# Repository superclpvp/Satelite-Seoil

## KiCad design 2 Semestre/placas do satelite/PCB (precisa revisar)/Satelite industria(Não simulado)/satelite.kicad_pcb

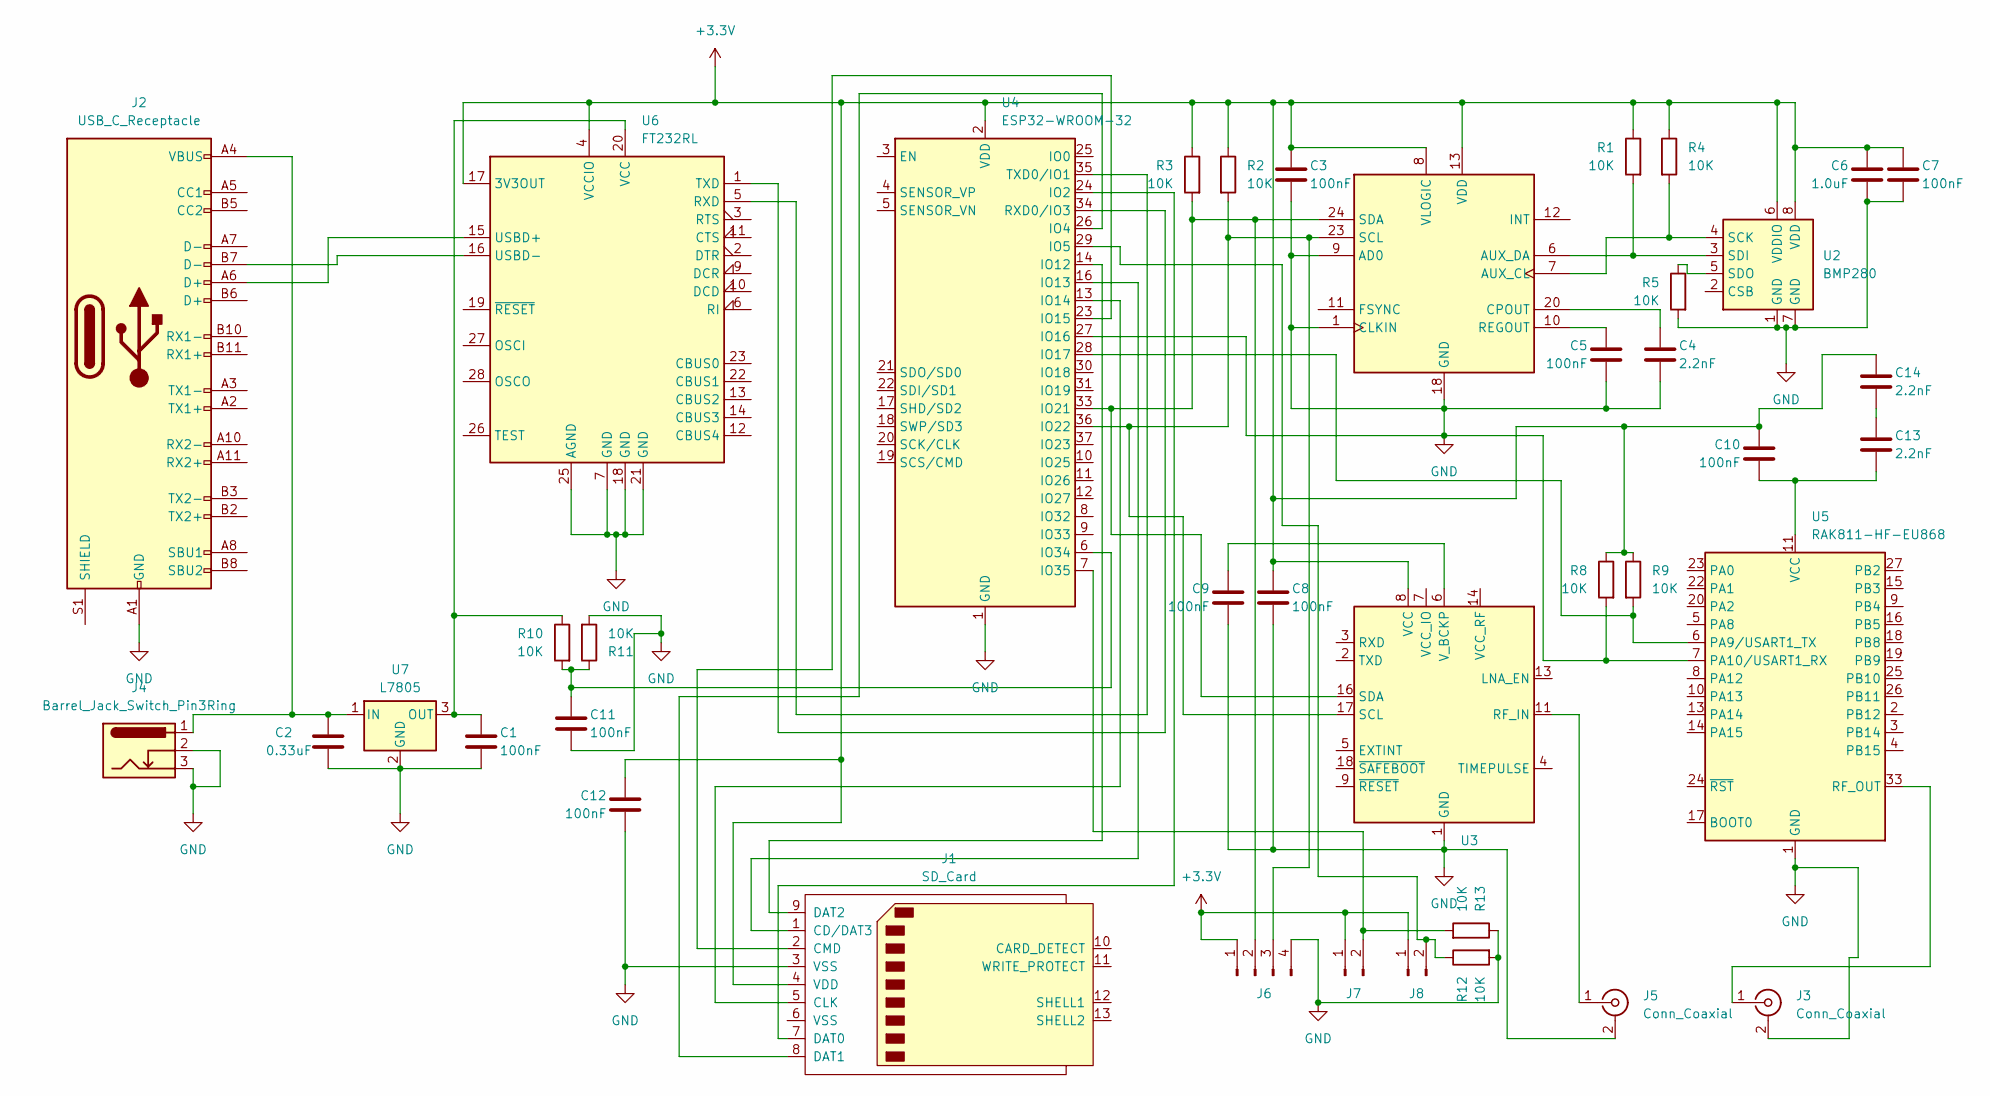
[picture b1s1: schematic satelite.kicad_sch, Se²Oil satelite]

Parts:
C1, C3, C5, C7, C8, C9, C10, C11, C12: 100nF; C_0805_2012Metric
C2: 0.33uF; C_0201_0603Metric
C4, C13, C14: 2.2nF; C_0201_0603Metric
C6: 1.0uF; C_0201_0603Metric
J1: SD_Card; microSD_HC_Hirose_DM3D-SF
J2: USB_C_Receptacle; USB_C_Receptacle_GCT_USB4085
J3, J5: Conn_Coaxial; U.FL_Hirose_U.FL-R-SMT-1_Vertical
J4: Barrel_Jack_Switch_Pin3Ring; BarrelJack_Horizontal
J6: Conn_01x04_Pin; PinHeader_1x04_P1.00mm_Vertical
J7, J8: Conn_01x02_Pin; PinHeader_1x02_P1.00mm_Vertical
R1, R2, R3, R4, R5, R8, R9, R10, R11, R12, R13: 10K; R_0805_2012Metric
U1: MPU-6050; InvenSense_QFN-24_4x4mm_P0.5mm
U2: BMP280; Bosch_LGA-8_2x2.5mm_P0.65mm_ClockwisePinNumbering
U3: MAX-M8Q; ublox_MAX
U4: ESP32-WROOM-32
U5: RAK811-HF-EU868; RAK811
U6: FT232RL; SSOP-28_5.3x10.2mm_P0.65mm
U7: L7805; TO-263-2

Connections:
+3.3V: C3.1, C6.1, C7.1, C8.1, C10.1, C12.1, C14.1, J1.4 (VDD), J6.1, J7.1, J8.1, R1.1, R2.1, R3.1, R4.1, R8.1, R9.1, U1.8 (VLOGIC), U1.13 (VDD), U2.6 (VDDIO), U2.8 (VDD), U3.8 (VCC), U4.2 (VDD), U6.4 (VCCIO), U6.17 (3V3OUT)
GND: C1.2, C2.2, C3.2, C4.2, C5.2, C6.2, C7.2, C8.2, C9.2, C11.2, C12.2, J1.3 (VSS), J2.A1 (GND), J2.A12 (GND), J2.B1 (GND), J2.B12 (GND), J3.2 (Ext), J4.2, J4.3, J5.2 (Ext), J6.4, R5.2, R8.2, R11.2, R12.2, R13.1, U1.1 (CLKIN), U1.9 (AD0), U1.18 (GND), U2.1 (GND), U2.7 (GND), U3.1 (GND), U3.10 (GND), U3.12 (GND), U4.1 (GND), U4.15 (GND), U4.27 (IO16), U4.38 (GND), U4.39 (GND), U5.1 (GND), U5.7 (PA10/USART1_RX), U5.12 (GND), U5.21 (GND), U5.28 (GND), U5.29 (GND), U5.30 (GND), U5.31 (GND), U5.32 (GND), U5.34 (GND), U6.7 (GND), U6.18 (GND), U6.21 (GND), U6.25 (AGND), U7.2 (GND)
unnamed: C13.1, C14.2
unnamed: J1.1 (CD/DAT3), U4.16 (IO13)
unnamed: J1.5 (CLK), U4.13 (IO14)
unnamed: J1.2 (CMD), U4.23 (IO15)
unnamed: J1.7 (DAT0), U4.24 (IO2)
unnamed: J1.8 (DAT1), U4.26 (IO4)
unnamed: J1.9 (DAT2), U4.14 (IO12)
unnamed: J3.1 (In), U5.33 (RF_OUT)
unnamed: J5.1 (In), U3.11 (RF_IN)
unnamed: J6.2, R3.2, U1.24 (SDA), U3.16 (SDA), U4.33 (IO21)
unnamed: J6.3, R2.2, U1.23 (SCL), U3.17 (SCL), U4.36 (IO22)
unnamed: J7.2, R13.2, U4.7 (IO35)
unnamed: J8.2, R12.1, U4.29 (IO5)
unnamed: R4.2, U1.7 (AUX_CL), U2.4 (SCK)
unnamed: R1.2, U1.6 (AUX_DA), U2.3 (SDI)
unnamed: C4.1, U1.20 (CPOUT)
unnamed: C5.1, U1.10 (REGOUT)
unnamed: R5.1, U2.5 (SDO)
unnamed: C9.1, U3.6 (V_BCKP)
unnamed: R9.2, U4.28 (IO17), U5.6 (PA9/USART1_TX)
unnamed: C11.1, R10.2, R11.1, U4.6 (IO34)
unnamed: U4.34 (RXD0/IO3), U6.1 (TXD)
unnamed: U4.35 (TXD0/IO1), U6.5 (RXD)
unnamed: C10.2, C13.2, U5.11 (VCC)
unnamed: J2.A6 (D+), U6.15 (USBD+)
unnamed: J2.B7 (D-), U6.16 (USBD-)
unnamed: C1.1, R10.1, U6.20 (VCC), U7.3 (OUT)
unnamed: C2.1, J2.A4 (VBUS), J2.A9 (VBUS), J2.B4 (VBUS), J2.B9 (VBUS), J4.1, U7.1 (IN)

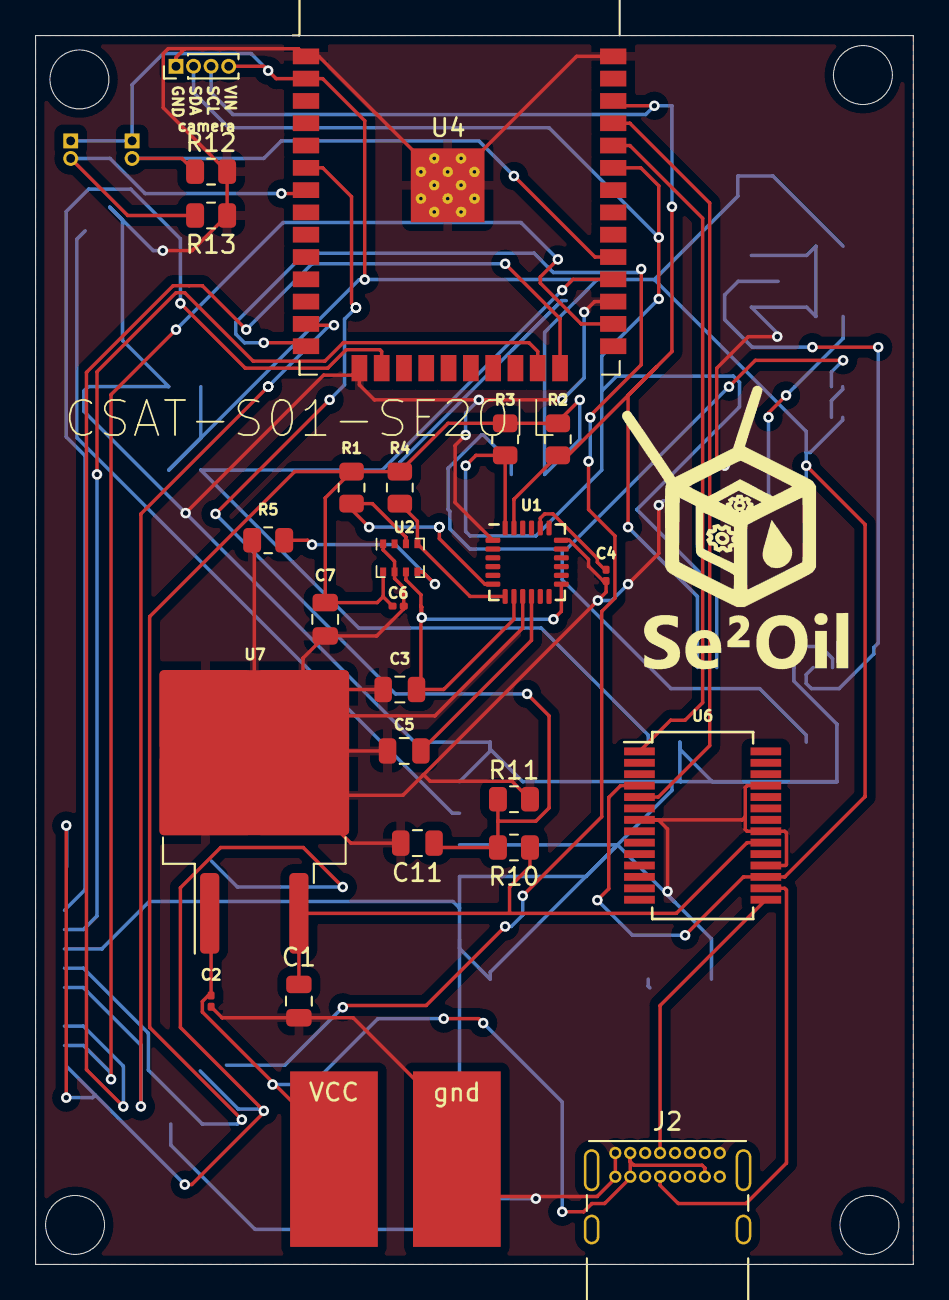
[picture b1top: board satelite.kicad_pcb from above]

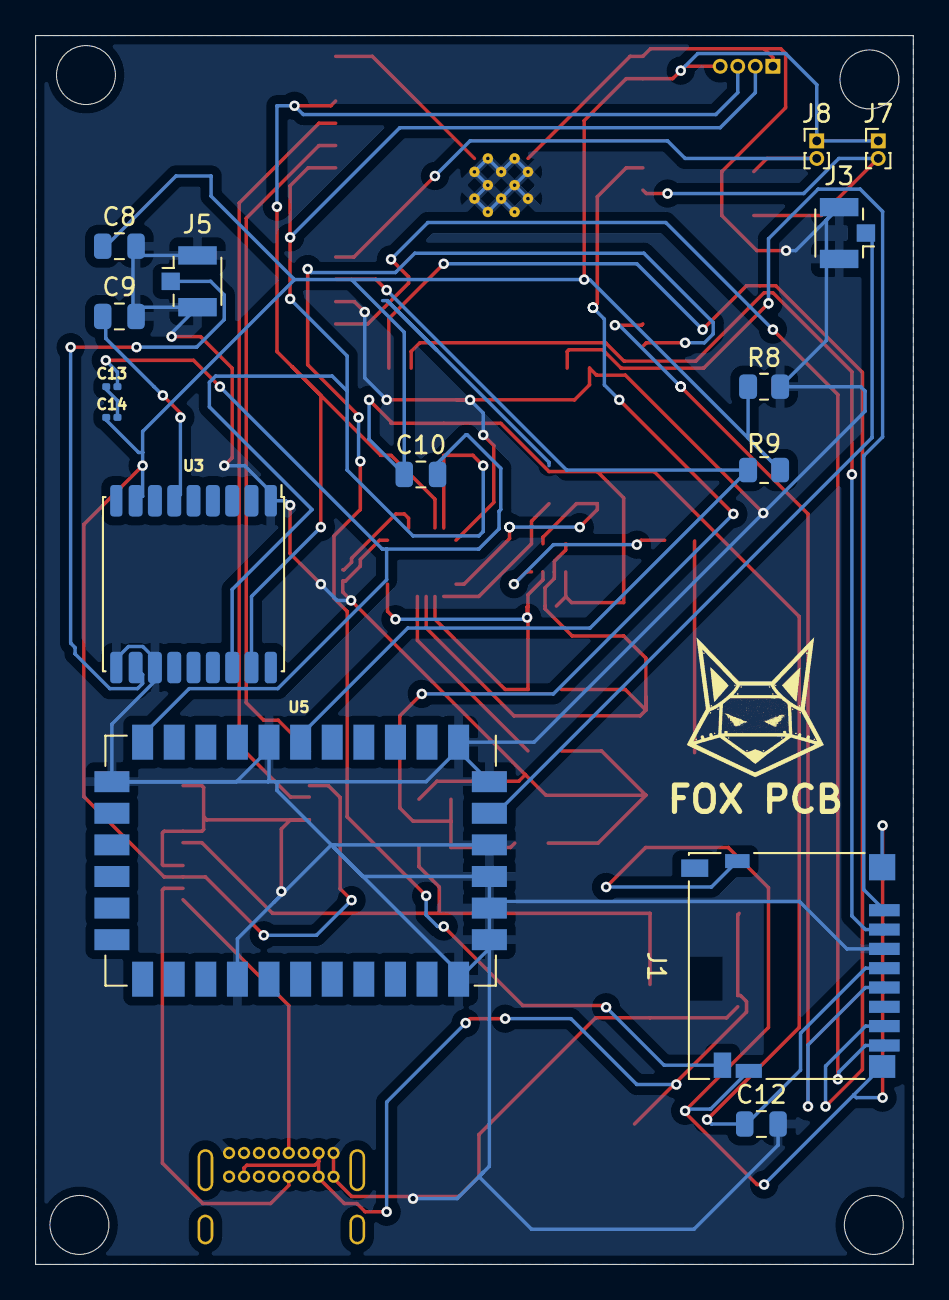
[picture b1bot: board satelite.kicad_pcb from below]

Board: 2 copper layers, 50.0 x 70.0 mm, 41 parts (16 on the bottom side), 30 nets.

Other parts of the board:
FOX PCB: LOGO; raposoBx10
VCC: SolderWirePad_1x01_SMD_5x10mm
gnd: SolderWirePad_1x01_SMD_5x10mm

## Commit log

2024-09-13 todos os arquivos do projeto
